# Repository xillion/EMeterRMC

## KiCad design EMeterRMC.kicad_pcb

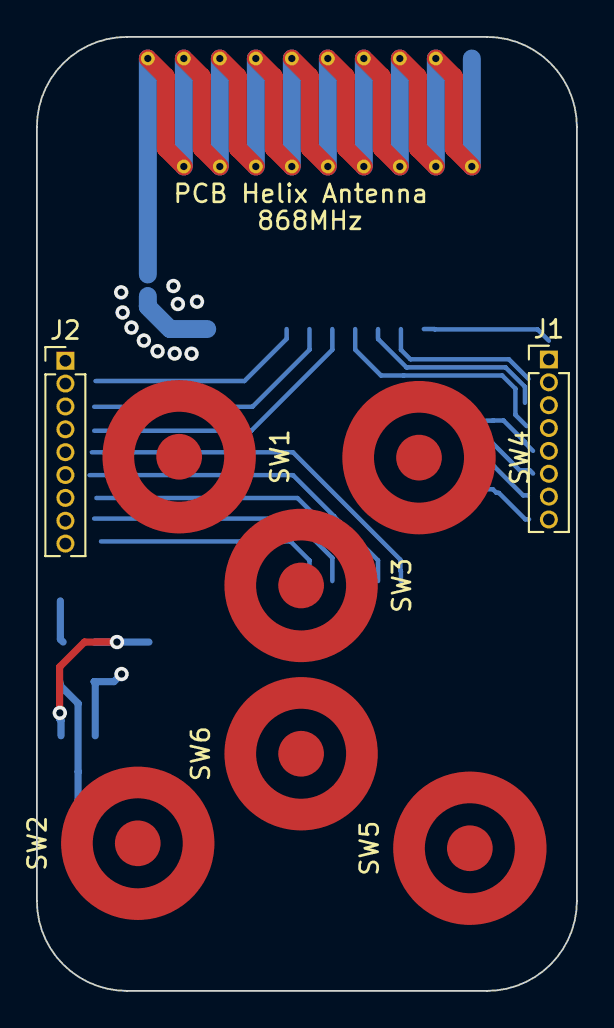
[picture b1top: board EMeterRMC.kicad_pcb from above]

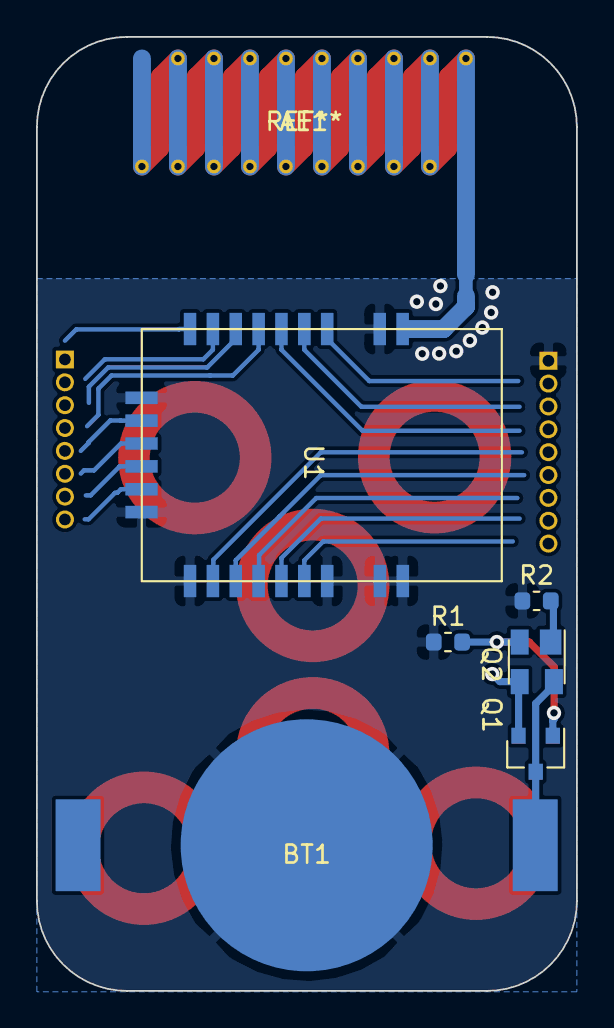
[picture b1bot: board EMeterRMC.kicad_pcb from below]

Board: 2 copper layers, 30.0 x 53.0 mm, 15 parts (7 on the bottom side), 21 nets.

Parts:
AE1: Antenna; Taxes_SWRA416_868MHz_Left
BT1: Battery_Cell; BatteryHolder_Linx_BAT-HLD-001
J1: Conn_01x08; PinHeader_1x08_P1.27mm_Vertical
J2: Conn_01x09; PinHeader_1x09_P1.27mm_Vertical
Q1: IRLML6402; SOT-23
Q2: BCV62; SOT-143
R1: 47.5k; R_0603_1608Metric
R2: 10k; R_0603_1608Metric
SW1: BTN1; SW_PCB_SNAPTRON_PNP-06
SW2: BTN3; SW_PCB_SNAPTRON_PNP-06
SW3: BTN5; SW_PCB_SNAPTRON_PNP-06
SW4: BTN2; SW_PCB_SNAPTRON_PNP-06
SW5: BTN4; SW_PCB_SNAPTRON_PNP-06
SW6: BTN6; SW_PCB_SNAPTRON_PNP-06
U1: E70-868T14S2; E70-868MS14

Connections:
BTN_COL1: J1.1, SW1.1, SW2.1, SW3.1, U1.22
BTN_COL2: J1.2, SW4.1, SW5.1, SW6.1
BTN_ROW1: J1.5, SW1.2, SW4.2, U1.16
BTN_ROW2: J1.6, SW2.2, SW5.2, U1.13
BTN_ROW3: J1.7, SW3.2, SW6.2, U1.12
GND: BT1.2, J2.1, R1.1, R2.1, U1.1, U1.2, U1.3, U1.9, U1.10, U1.15, U1.23
unnamed: AE1.1, U1.24
unnamed: BT1.1, Q1.3, Q2.4
unnamed: J1.3, U1.20
unnamed: J1.4, U1.17
unnamed: J1.8, U1.11
unnamed: J2.2, Q1.2, Q2.3, U1.8
unnamed: J2.3, U1.19
unnamed: J2.4, U1.18
unnamed: J2.5, U1.14
unnamed: J2.6, U1.5
unnamed: J2.7, U1.4
unnamed: J2.8, U1.6
unnamed: J2.9, U1.7
unnamed: Q1.1, Q2.2, R1.2
unnamed: Q2.1, R2.2

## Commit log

2019-08-27 corrected pcd
